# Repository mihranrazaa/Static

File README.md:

# Static

A RP2040 based development board made by me ofc :). it is an attempt to recreate a pico type board to improve my pcb designing skills. 

# Schematics and PCB images

---

---

---

All the files are available in Kicad folder.

## Production
The gerber file is present in the production folder there is also a bom.csv which is similar to the one present below

## Motivation

### Why
Building a arduino kind of development board is already cool to me, but designing one helps me improve my pcb skills too.. 

## How
You need soldering iron, goood hands all the components and you should be good. I have also added 3d file for reference. 

# BOM

| Item                  | Cost   |
| --------------------- | ------ |
| PCB                   | 40 usd |
| total components cost | 6usd   |
| Total approx          | 49usd  |

**Please refer to the bom.csv in production for all the components**

---

made with <3 by [mihranrazaa](https://mihranrazaa.info/)

BYEEE

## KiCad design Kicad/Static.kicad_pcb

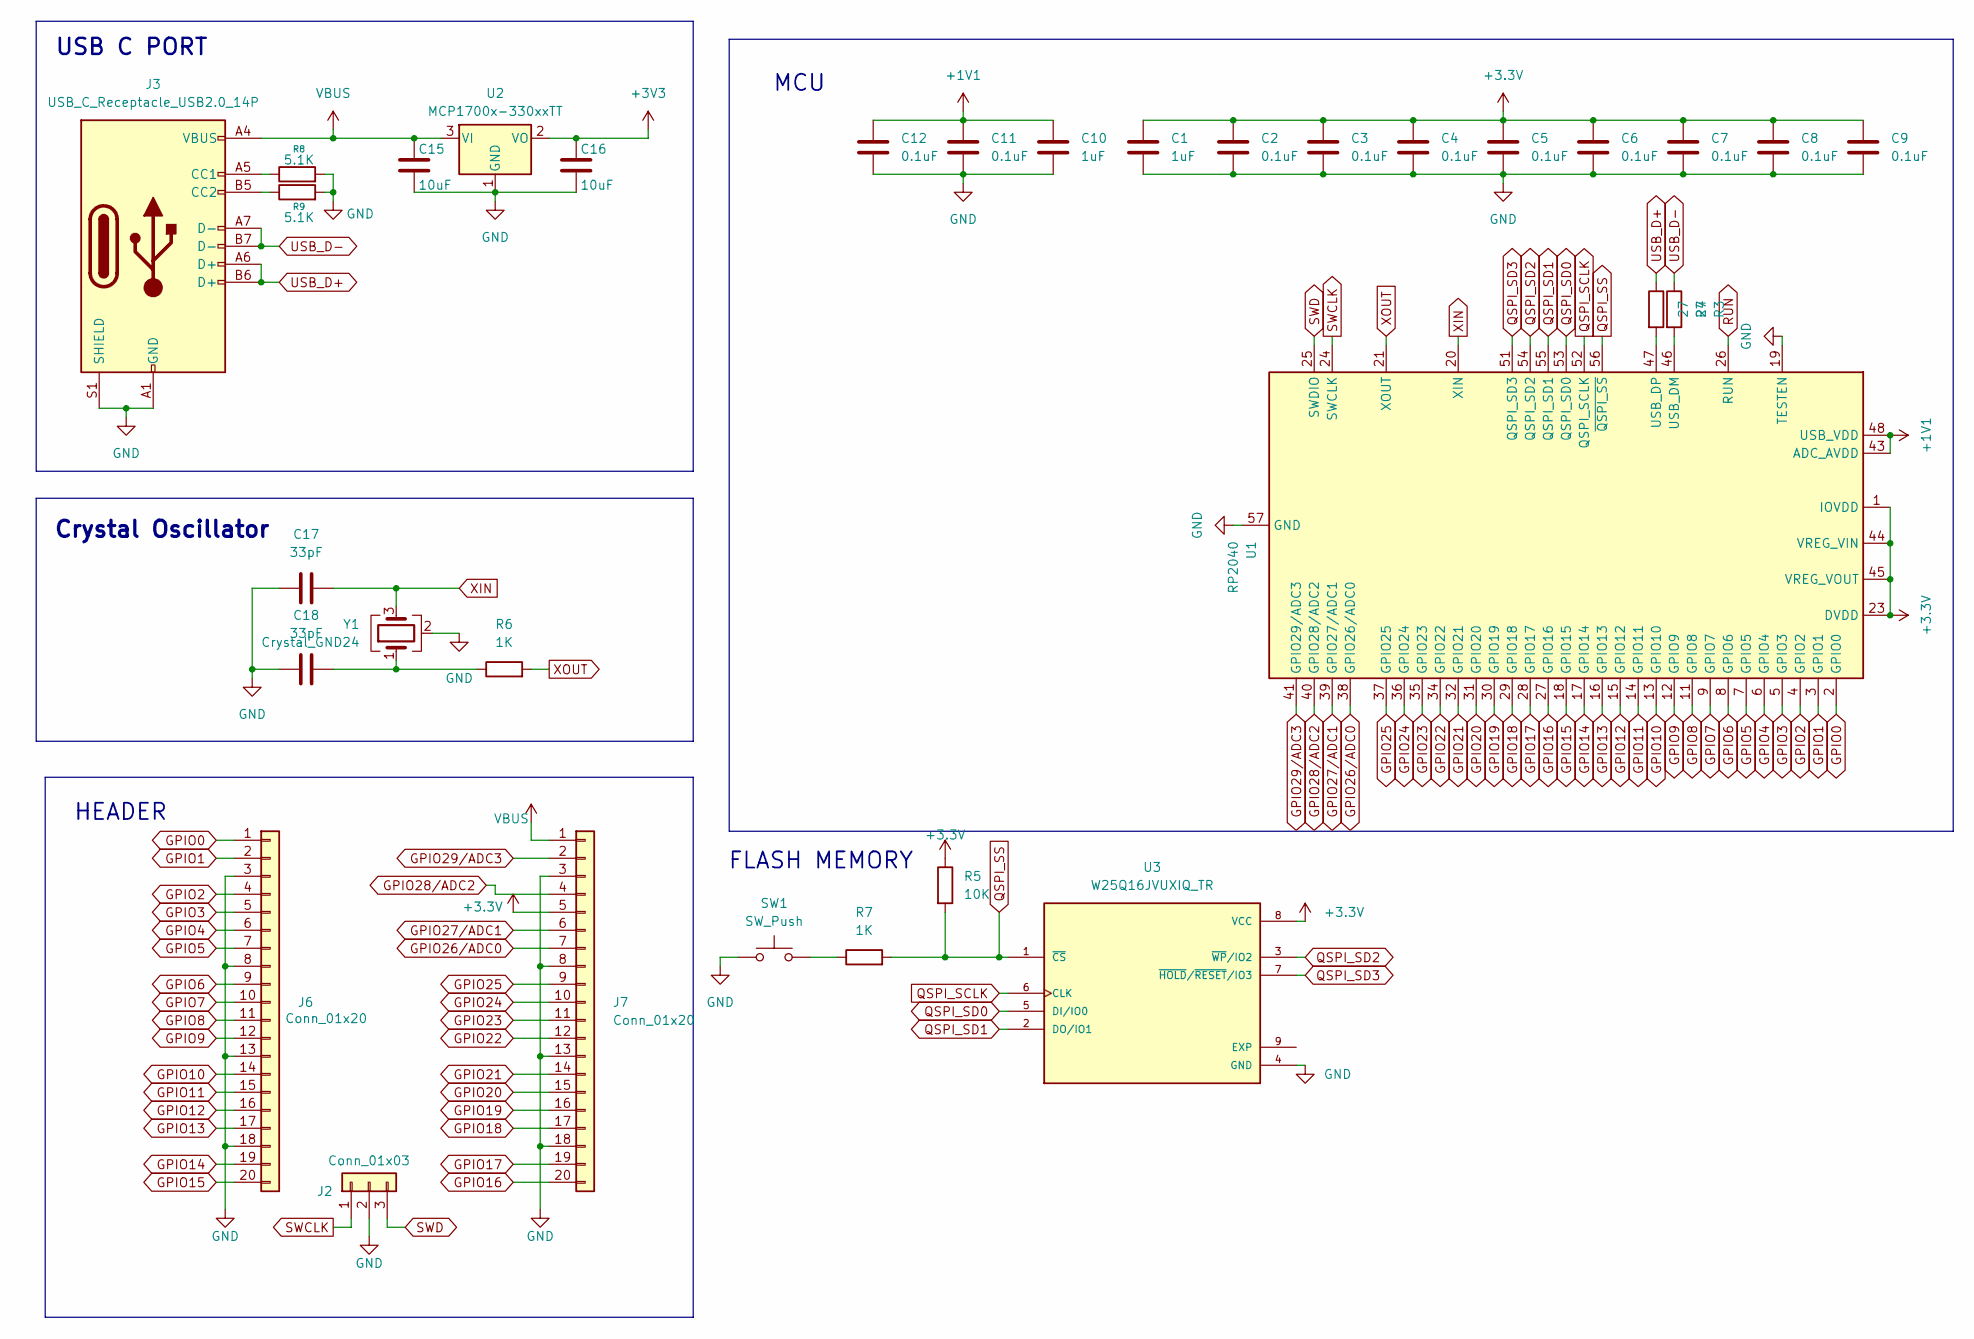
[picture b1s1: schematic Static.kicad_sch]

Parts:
C1, C10: 1uF; C_0402_1005Metric
C2, C3, C4, C5, C6, C7, C8, C9, C11, C12: 0.1uF; C_0402_1005Metric
C15, C16: 10uF; C_0603_1608Metric
C17, C18: 33pF; C_0402_1005Metric
J2: Conn_01x03; PinHeader_1x03_P2.54mm_Vertical
J3: USB_C_Receptacle_USB2.0_14P; USB_C_Receptacle_HRO_TYPE-C-31-M-12
J6, J7: Conn_01x20; PinHeader_1x20_P2.54mm_Vertical
R3, R4: 27; R_0402_1005Metric
R5: 10K; R_0402_1005Metric
R6, R7: 1K; R_0402_1005Metric
R8, R9: 5.1K; R_0402_1005Metric
SW1: SW_Push; SW_TS-1088-AR02016
U1: RP2040; QFN-56-1EP_7x7mm_P0.4mm_EP3.2x3.2mm
U2: MCP1700x-330xxTT; SOT-23
U3: W25Q16JVUXIQ_TR; IC_W25Q16JVUXIQ_TR; PARTREV H
Y1: Crystal_GND24; SMD_2MSB4SI_YXC

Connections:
+1V1: C10.1, C11.1, C12.1, U1.43 (ADC_AVDD), U1.48 (USB_VDD)
+3.3V: C1.1, C2.1, C3.1, C4.1, C5.1, C6.1, C7.1, C8.1, C9.1, J7.5, R5.1, U1.1 (IOVDD), U1.10 (IOVDD), U1.22 (IOVDD), U1.23 (DVDD), U1.33 (IOVDD), U1.42 (IOVDD), U1.44 (VREG_VIN), U1.45 (VREG_VOUT), U1.49 (IOVDD), U1.50 (DVDD), U3.8 (VCC)
+3V3: C16.1, U2.2 (VO)
GND: C1.2, C2.2, C3.2, C4.2, C5.2, C6.2, C7.2, C8.2, C9.2, C10.2, C11.2, C12.2, C15.2, C16.2, C17.1, C18.1, J2.2, J3.A1 (GND), J3.A12 (GND), J3.B1 (GND), J3.B12 (GND), J3.S1 (SHIELD), J6.3, J6.8, J6.13, J6.18, J7.3, J7.8, J7.13, J7.18, R8.2, R9.2, SW1.1, U1.19 (TESTEN), U1.57 (GND), U2.1 (GND), U3.4 (GND), Y1.2 (G), Y1.4 (G)
GPIO0: J6.1, U1.2 (GPIO0)
GPIO1: J6.2, U1.3 (GPIO1)
GPIO2: J6.4, U1.4 (GPIO2)
GPIO3: J6.5, U1.5 (GPIO3)
GPIO4: J6.6, U1.6 (GPIO4)
GPIO5: J6.7, U1.7 (GPIO5)
GPIO6: J6.9, U1.8 (GPIO6)
GPIO7: J6.10, U1.9 (GPIO7)
GPIO8: J6.11, U1.11 (GPIO8)
GPIO9: J6.12, U1.12 (GPIO9)
GPIO10: J6.14, U1.13 (GPIO10)
GPIO11: J6.15, U1.14 (GPIO11)
GPIO12: J6.16, U1.15 (GPIO12)
GPIO13: J6.17, U1.16 (GPIO13)
GPIO14: J6.19, U1.17 (GPIO14)
GPIO15: J6.20, U1.18 (GPIO15)
GPIO16: J7.20, U1.27 (GPIO16)
GPIO17: J7.19, U1.28 (GPIO17)
GPIO18: J7.17, U1.29 (GPIO18)
GPIO19: J7.16, U1.30 (GPIO19)
GPIO20: J7.15, U1.31 (GPIO20)
GPIO21: J7.14, U1.32 (GPIO21)
GPIO22: J7.12, U1.34 (GPIO22)
GPIO23: J7.11, U1.35 (GPIO23)
GPIO24: J7.10, U1.36 (GPIO24)
GPIO25: J7.9, U1.37 (GPIO25)
GPIO26/ADC0: J7.7, U1.38 (GPIO26/ADC0)
GPIO27/ADC1: J7.6, U1.39 (GPIO27/ADC1)
GPIO28/ADC2: J7.4, U1.40 (GPIO28/ADC2)
GPIO29/ADC3: J7.2, U1.41 (GPIO29/ADC3)
unnamed: C18.2, R6.1, Y1.1
unnamed: J3.A5 (CC1), R8.1
unnamed: J3.B5 (CC2), R9.1
unnamed: R7.1, SW1.2
unnamed: R3.2, U1.46 (USB_DM)
unnamed: R4.2, U1.47 (USB_DP)
QSPI_SCLK: U1.52 (QSPI_SCLK), U3.6 (CLK)
QSPI_SD0: U1.53 (QSPI_SD0), U3.5 (DI/IO0)
QSPI_SD1: U1.55 (QSPI_SD1), U3.2 (DO/IO1)
QSPI_SD2: U1.54 (QSPI_SD2), U3.3 (~WP/IO2)
QSPI_SD3: U1.51 (QSPI_SD3), U3.7 (~HOLD/~RESET/IO3)
QSPI_SS: R5.2, R7.2, U1.56 (~QSPI_SS), U3.1 (~CS)
RUN: U1.26 (RUN)
SWCLK: J2.1, U1.24 (SWCLK)
SWD: J2.3, U1.25 (SWDIO)
USB_D+: J3.A6 (D+), J3.B6 (D+), R4.1
USB_D-: J3.A7 (D-), J3.B7 (D-), R3.1
VBUS: C15.1, J3.A4 (VBUS), J3.A9 (VBUS), J3.B4 (VBUS), J3.B9 (VBUS), J7.1, U2.3 (VI)
XIN: C17.2, U1.20 (XIN), Y1.3
XOUT: R6.2, U1.21 (XOUT)

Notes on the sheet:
Crystal Oscillator
MCU
FLASH MEMORY
USB C PORT
HEADER

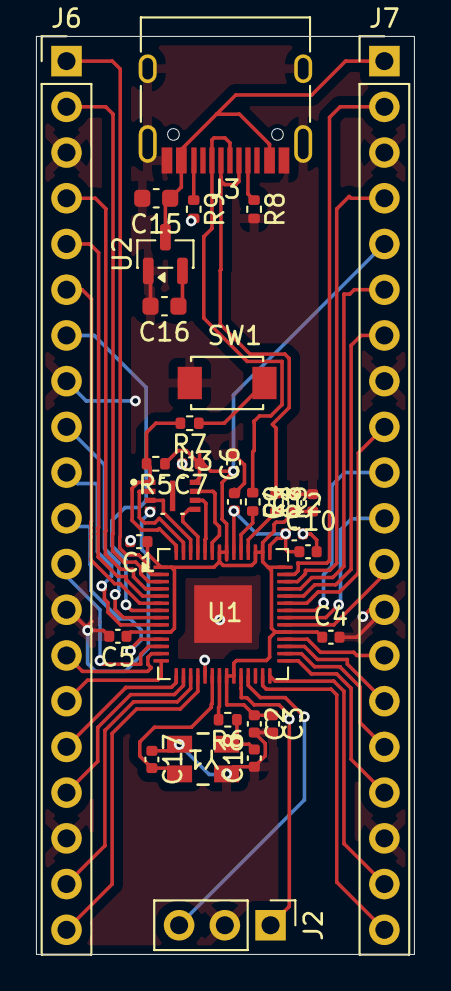
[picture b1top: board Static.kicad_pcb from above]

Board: 2 copper layers, 21.0 x 51.0 mm, 32 parts (0 on the bottom side), 53 nets.

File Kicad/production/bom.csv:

Designator,Footprint,Quantity,Value,LCSC Part #
"C1, C10",0402,2,1uF,
"C11, C12, C2, C3, C4, C5, C6, C7, C8, C9",0402,10,0.1uF,
"C15, C16",0603,2,10uF,
"C17, C18",0402,2,33pF,
J2,PinHeader_1x03_P2.54mm_Vertical,1,Conn_01x03,
J3,USB_C_Receptacle_HRO_TYPE-C-31-M-12,1,USB_C_Receptacle_USB2.0_14P,
"J6, J7",PinHeader_1x20_P2.54mm_Vertical,2,Conn_01x20,
"R3, R4",0402,2,27,
R5,0402,1,10K,
"R6, R7",0402,2,1K,
"R8, R9",0402,2,5.1K,
SW1,SW_TS-1088-AR02016,1,SW_Push,
U1,QFN-56-1EP_7x7mm_P0.4mm_EP3.2x3.2mm,1,RP2040,
U2,SOT-23,1,MCP1700x-330xxTT,
U3,IC_W25Q16JVUXIQ_TR,1,W25Q16JVUXIQ_TR,
Y1,SMD_2MSB4SI_YXC,1,Crystal_GND24,

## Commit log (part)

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2026-04-27 Update JOURNAL.md with dev board progress
    Document progress on building a dev board with RP2040, including schematic updates and component details.
2026-04-29 Document schematic design progress in JOURNAL.md
    Added detailed journal entries about schematic design progress, including issues with components and software.
2026-04-30 Update journal with completed schematics and design notes
    Documented the completion of schematics and design process for the project, including details about components used and future plans.
2026-05-05 Update JOURNAL with PCB design and routing notes
    Document progress on PCB routing and design adjustments after a break due to a family event. Discuss plans for pin headers and routing considerations.
2026-05-07 Update journal with project shape changes and progress
    Document changes in project shape and components used. Include updates on progress and challenges faced during the design process.
